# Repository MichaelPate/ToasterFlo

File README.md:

# ToasterFlo
 Control a toaster oven to make PCB assemblies

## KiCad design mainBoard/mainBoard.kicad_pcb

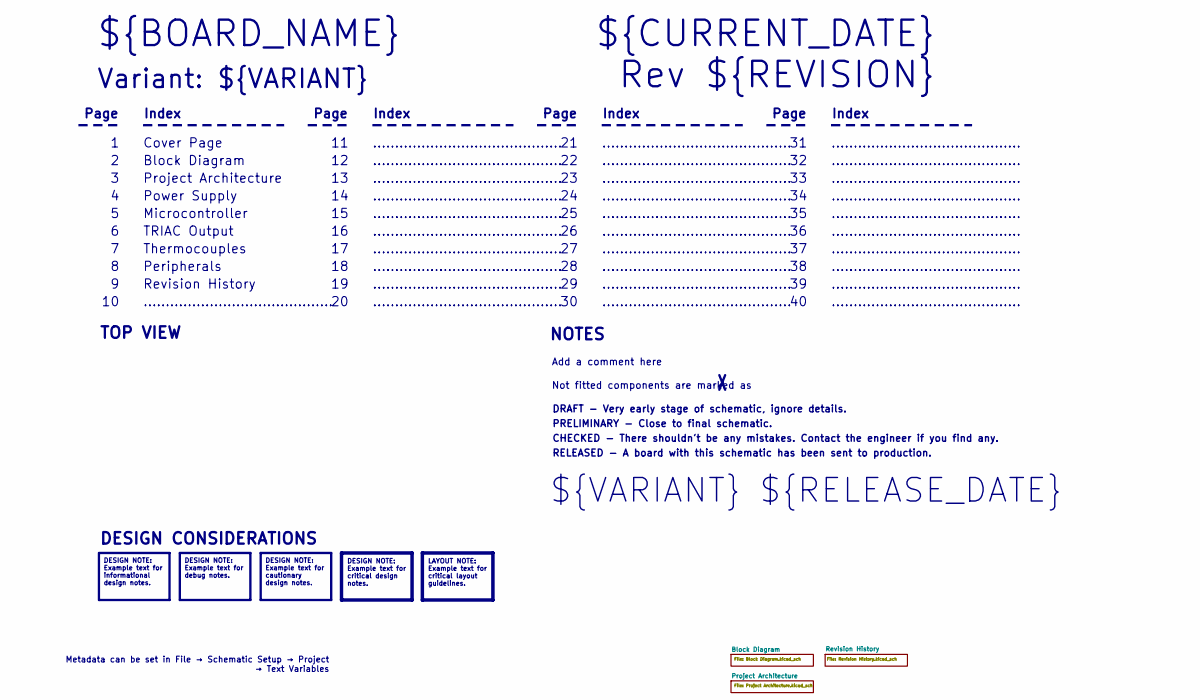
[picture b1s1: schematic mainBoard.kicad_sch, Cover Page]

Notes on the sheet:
...........................................
RELEASED - A board with this schematic has been sent to production.
Page
TOP VIEW
Revision History
Peripherals
Not fitted components are marked as
Index
PRELIMINARY - Close to final schematic.
${VARIANT} ${RELEASE_DATE}
Power Supply
${CURRENT_DATE}
Variant: ${VARIANT}
Rev ${REVISION}
Microcontroller
${BOARD_NAME}
DRAFT - Very early stage of schematic, ignore details.
TRIAC Output
Block Diagram
Add a comment here
Cover Page
NOTES
Project Architecture
CHECKED - There shouldn't be any mistakes. Contact the engineer if you find any.
DESIGN CONSIDERATIONS
Thermocouples
Metadata can be set in File → Schematic Setup → Project → Text Variables
DESIGN NOTE: Example text for informational design notes.
LAYOUT NOTE: Example text for critical layout guidelines.
DESIGN NOTE: Example text for cautionary design notes.
DESIGN NOTE: Example text for debug notes.
DESIGN NOTE: Example text for critical design notes.

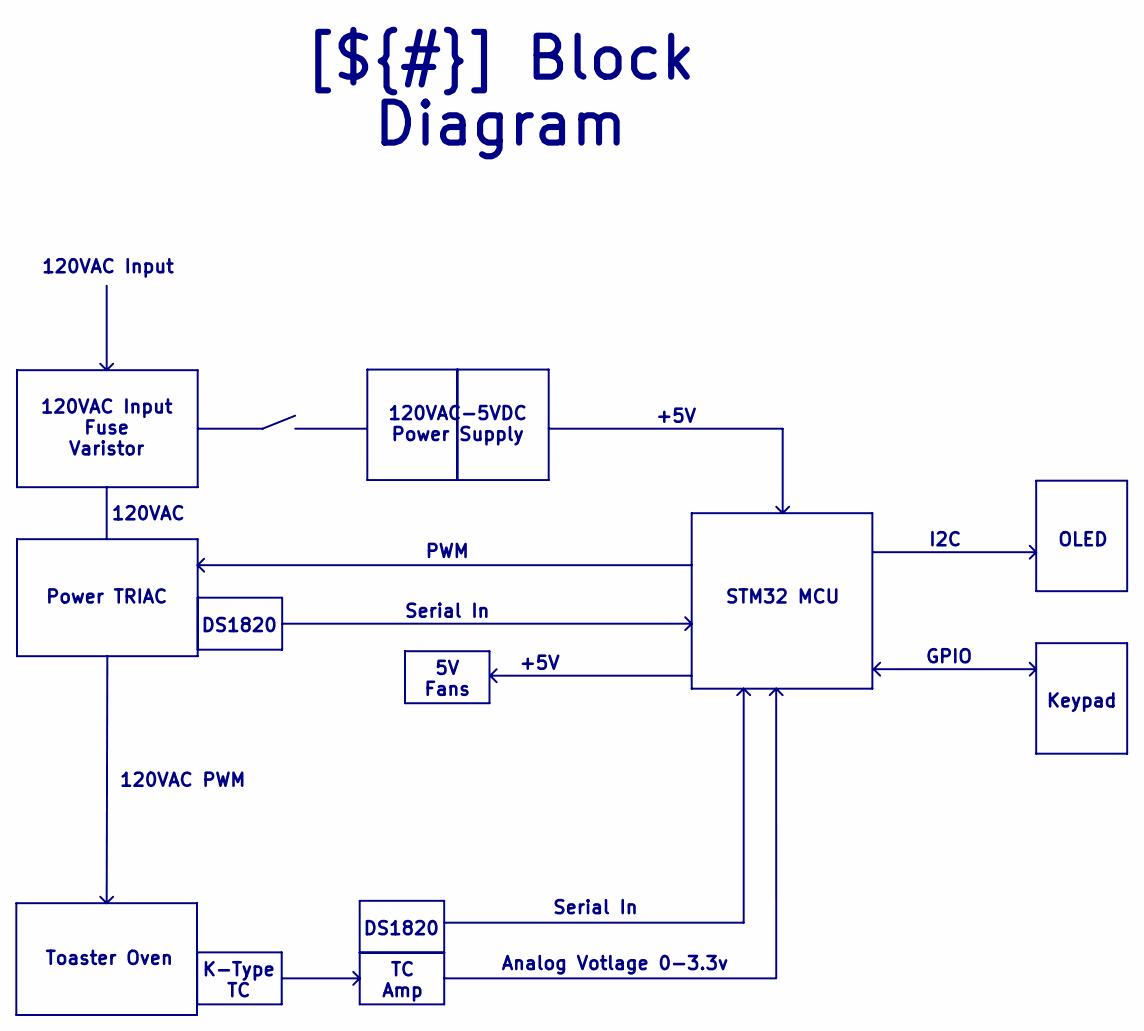
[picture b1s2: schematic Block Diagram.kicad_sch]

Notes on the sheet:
5V Fans
OLED
+5V
Serial In
GPIO
120VAC Input
TC Amp
K-Type TC
Toaster Oven
120VAC-5VDC Power Supply
120VAC Input Fuse Varistor
DS1820
Analog Votlage 0-3.3v
I2C
Power TRIAC
STM32 MCU
PWM
Keypad
120VAC PWM
120VAC
[${#}] ${TITLE}

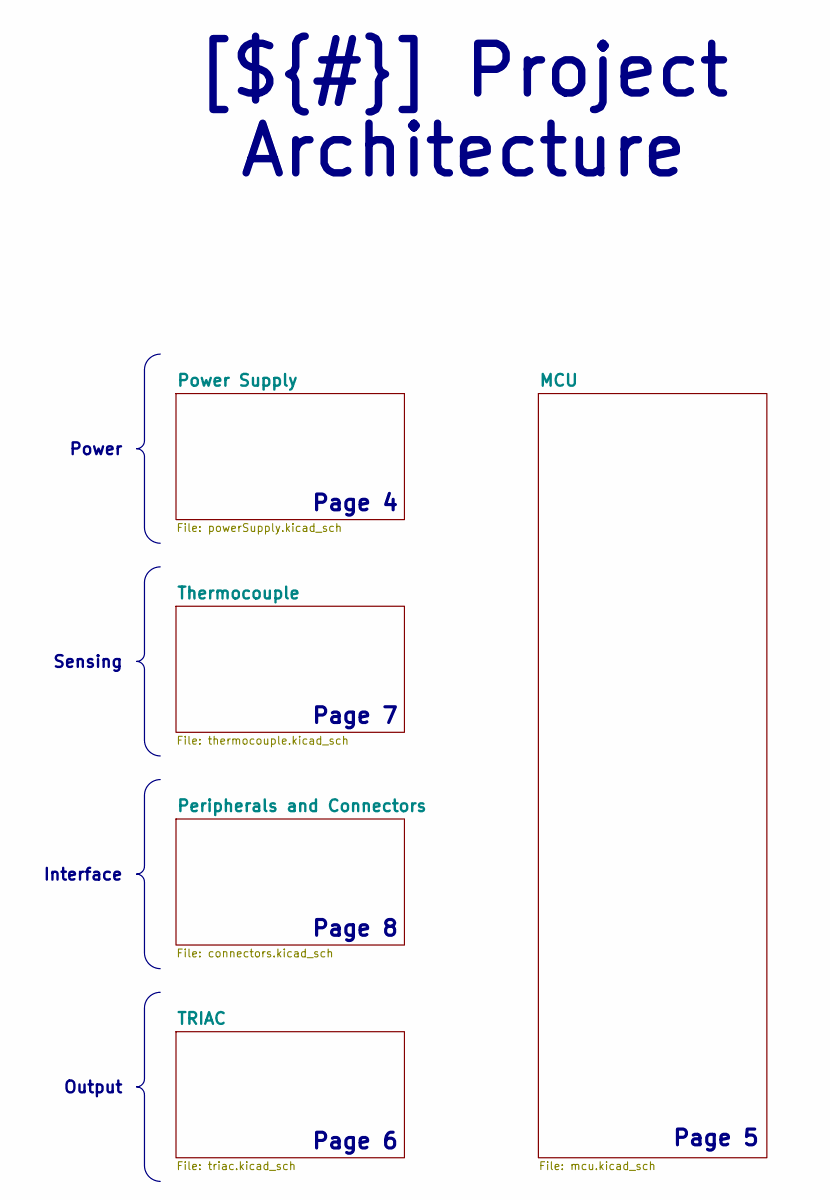
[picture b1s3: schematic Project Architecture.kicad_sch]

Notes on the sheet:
Page 7
Page 8
Page 6
Page 5
Page 4
Power
Sensing
[${#}] ${TITLE}
Interface
Output

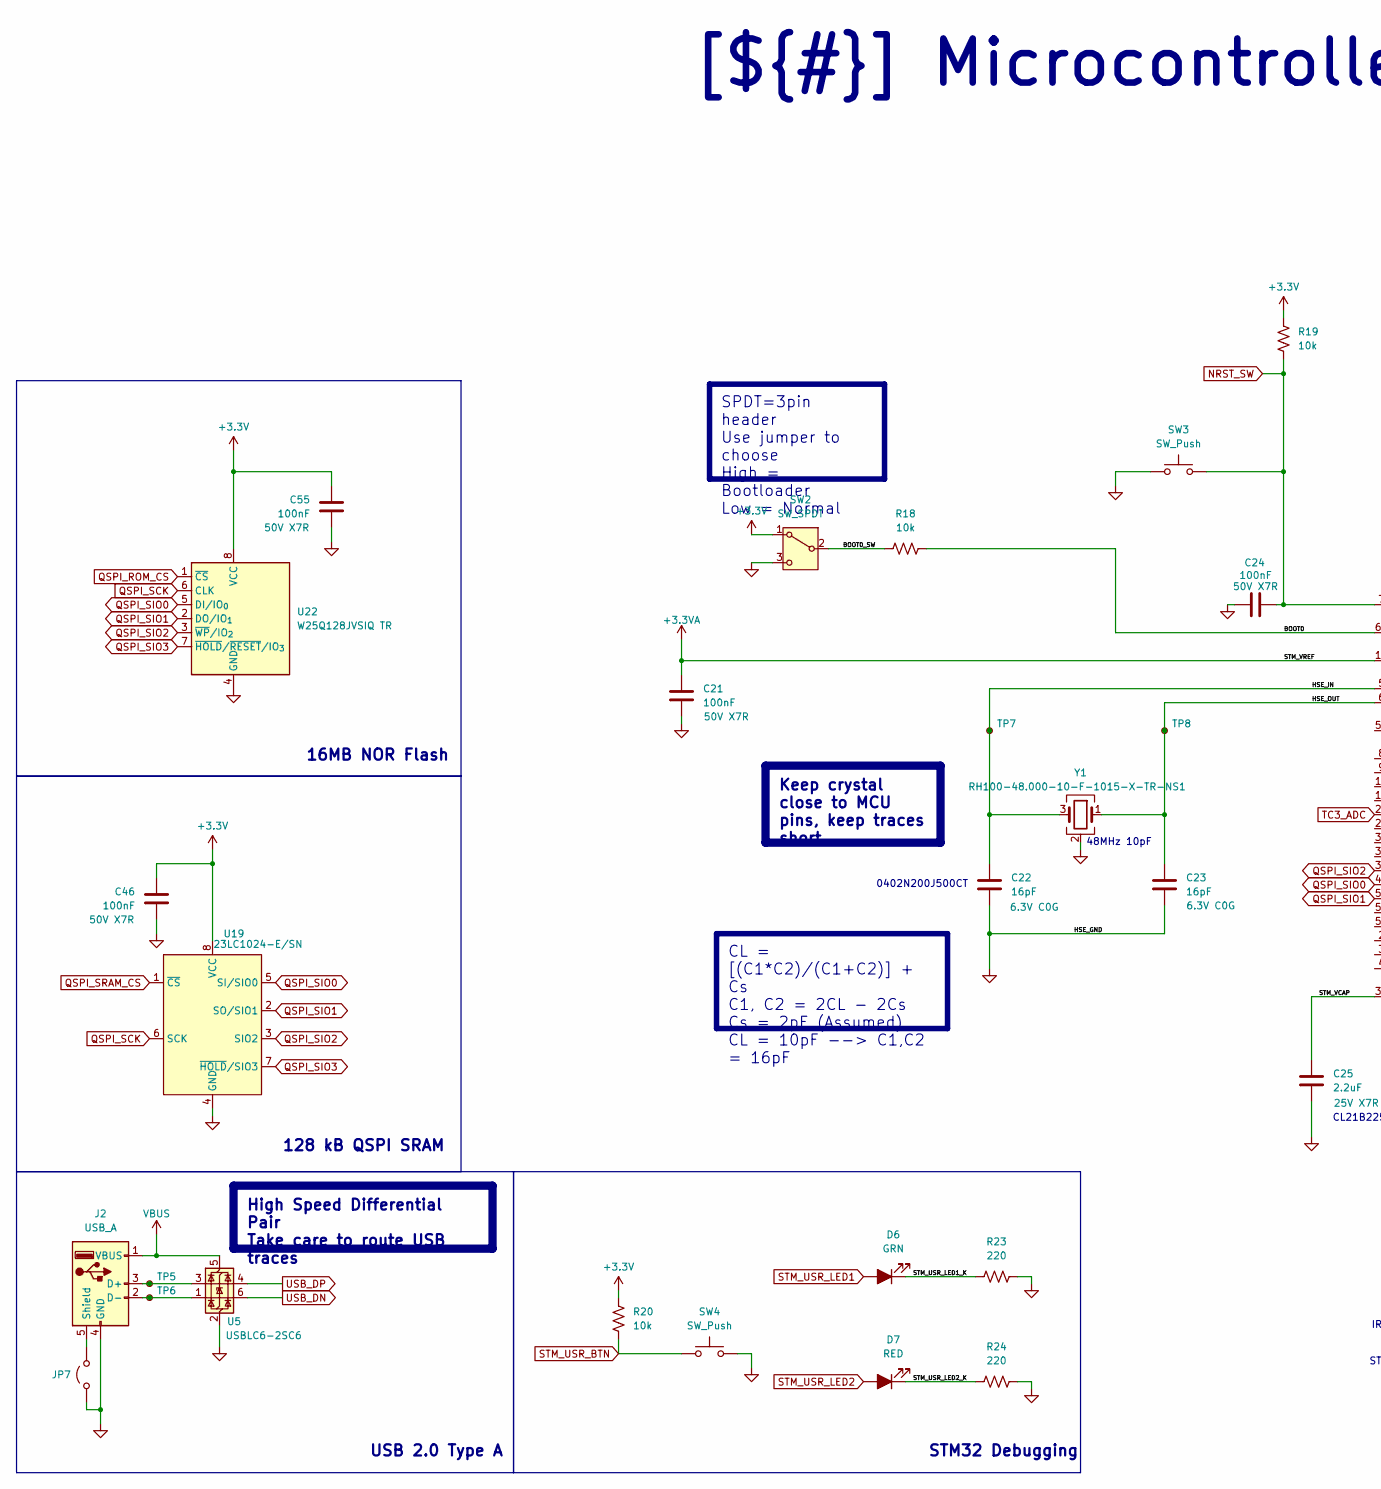
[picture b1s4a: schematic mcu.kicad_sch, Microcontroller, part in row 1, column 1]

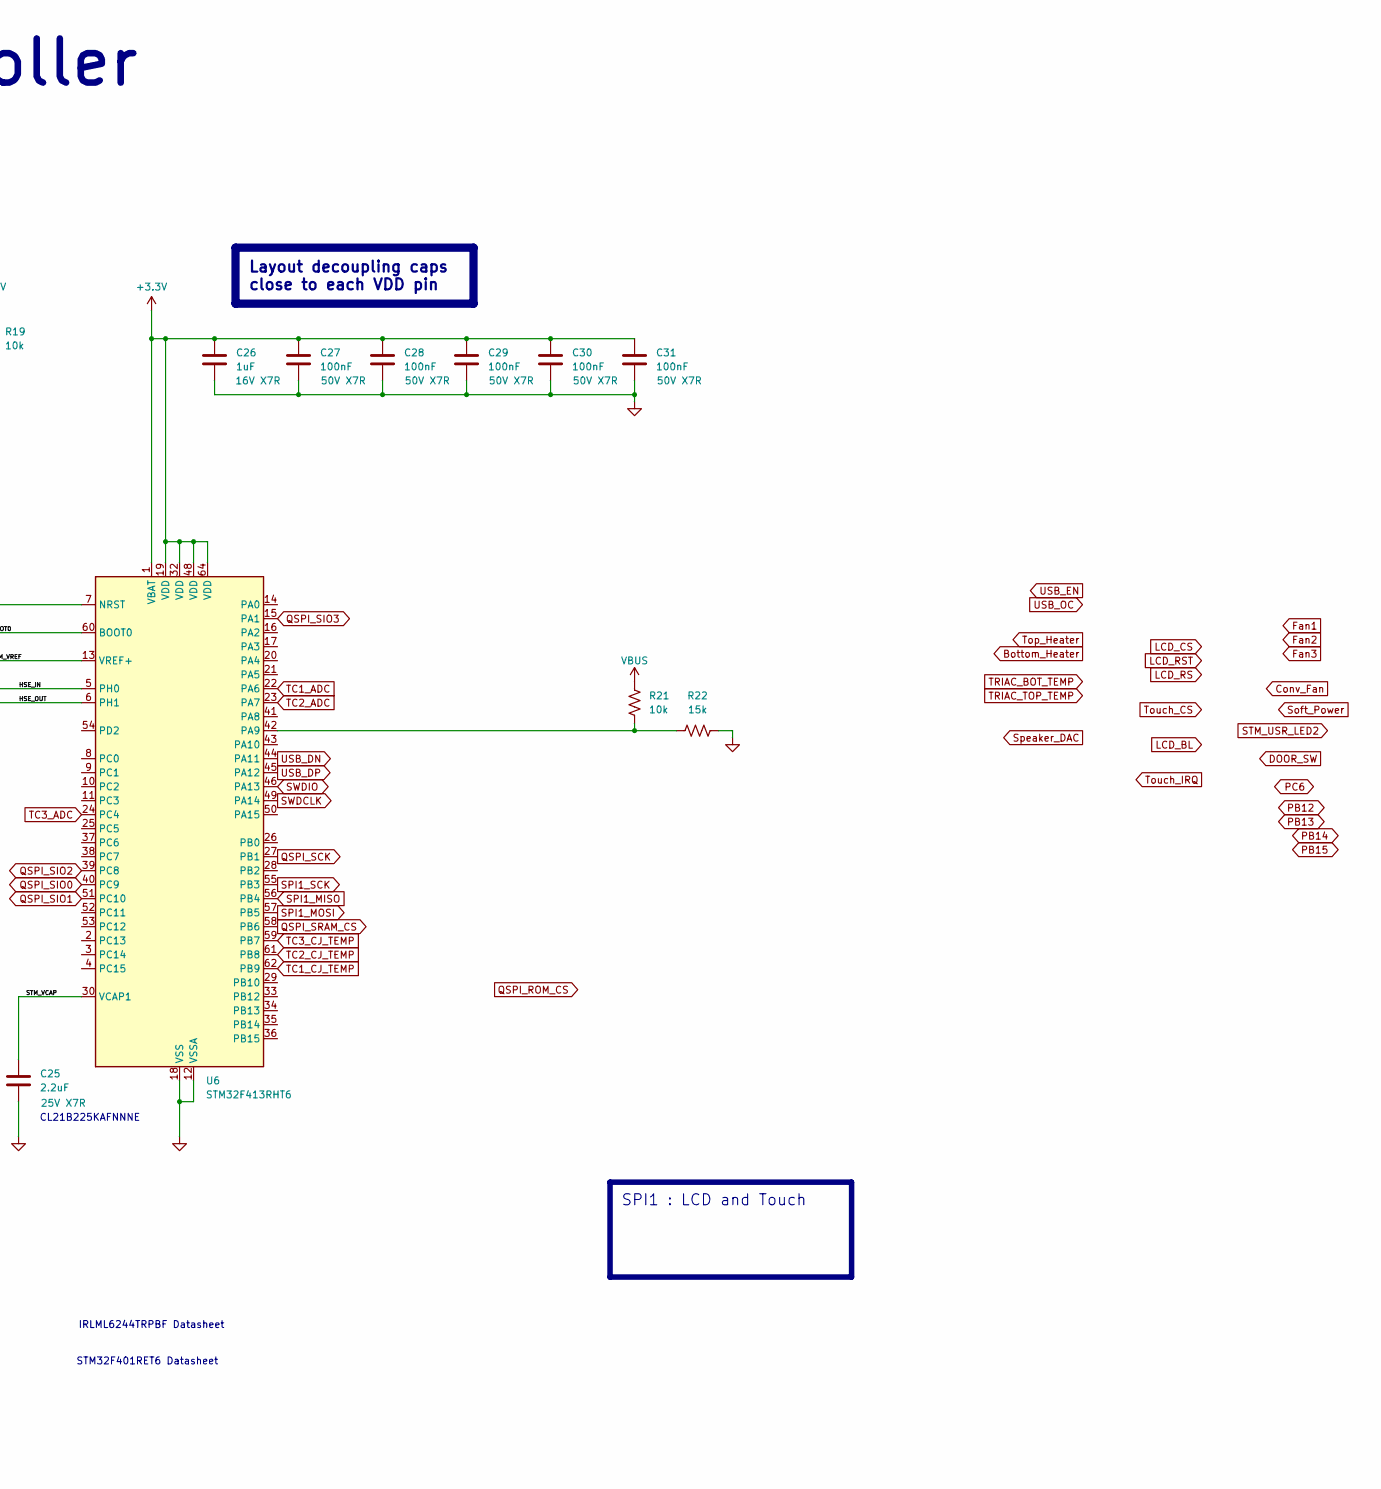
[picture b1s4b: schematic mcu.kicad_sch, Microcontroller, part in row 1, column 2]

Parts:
C21, C24, C27, C28, C29, C30, C31, C46, C55: 100nF; C_0603_1608Metric_Pad1.08x0.95mm_HandSolder
C22, C23: 16pF; C_0402_1005Metric_Pad0.74x0.62mm_HandSolder; part number 0402N200J500CT
C25: 2.2uF; C_0805_2012Metric_Pad1.18x1.45mm_HandSolder; part number CL21B225KAFNNNE
C26: 1uF; C_0805_2012Metric_Pad1.18x1.45mm_HandSolder
D6: GRN; LED_0603_1608Metric_Pad1.05x0.95mm_HandSolder
D7: RED; LED_0603_1608Metric_Pad1.05x0.95mm_HandSolder
J2: USB_A; USB_A_Connfly_DS1095
JP7: Jumper_2_Open; SolderJumper-2_P1.3mm_Open_TrianglePad1.0x1.5mm
R18, R19, R20, R21: 10k; R_0603_1608Metric_Pad0.98x0.95mm_HandSolder
R22: 15k; R_0603_1608Metric_Pad0.98x0.95mm_HandSolder
R23, R24: 220; R_0603_1608Metric_Pad0.98x0.95mm_HandSolder
SW2: SW_SPDT; PinHeader_1x03_P2.54mm_Vertical
SW3, SW4: SW_Push; SW_PUSH_6mm_H8.5mm
TP5, TP6, TP7, TP8: TestPoint_Small; TestPoint_Pad_D1.0mm
U5: USBLC6-2SC6; SOT-23-6
U6: STM32F413RHT6; LQFP-64_10x10mm_P0.5mm
U19: 23LC1024-E/SN; SOIC-8_5.3x5.3mm_P1.27mm
U22: W25Q128JVSIQ TR; SOIC-8_5.3x5.3mm_P1.27mm
Y1: RH100-48.000-10-F-1015-X-TR-NS1; Crystal_SMD_3225-4Pin_3.2x2.5mm

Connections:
+3.3V: C26.1, C27.1, C28.1, C29.1, C30.1, C31.1, C46.1, C55.1, R19.1, R20.1, SW2.1 (A), U6.1 (VBAT), U6.19 (VDD), U6.32 (VDD), U6.48 (VDD), U6.64 (VDD), U19.8 (VCC), U22.8 (VCC); also elsewhere on the board
+3.3VA: C21.1, U6.13 (VREF+); also elsewhere on the board
/Project Architecture/MCU/BOOT0: R18.2, U6.60 (BOOT0)
/Project Architecture/MCU/BOOT0_SW: R18.1, SW2.2 (B)
/Project Architecture/MCU/HSE_IN: C22.1, TP7.1 (1_1), U6.5 (PH0), Y1.3
/Project Architecture/MCU/HSE_OUT: C23.1, TP8.1 (1_1), U6.6 (PH1), Y1.1
/Project Architecture/MCU/STM_USR_LED1_K: D6.1 (K), R23.1
/Project Architecture/MCU/STM_USR_LED2_K: D7.1 (K), R24.1
/Project Architecture/MCU/STM_VCAP: C25.1, U6.30 (VCAP1)
GND: C21.2, C22.2, C23.2, C24.1, C25.2, C26.2, C27.2, C28.2, C29.2, C30.2, C31.2, C46.2, C55.2, J2.4 (GND), JP7.1 (A), R22.2, R23.2, R24.2, SW2.3 (C), SW3.1, SW4.2, U5.2 (GND), U6.12 (VSSA), U6.18 (VSS), U6.31 (VSS), U6.47 (VSS), U6.63 (VSS), U19.4 (GND), U22.4 (GND), Y1.2 (G), Y1.4 (G); also elsewhere on the board
NRST_SW: C24.2, R19.2, SW3.2, U6.7 (NRST); also elsewhere on the board
unnamed: J2.3 (D+), TP5.1 (1_1), U5.3 (I/O1)
unnamed: J2.2 (D-), TP6.1 (1_1), U5.1 (I/O2)
unnamed: J2.5 (Shield), JP7.2 (B)
unnamed: R21.1, R22.1, U6.42 (PA9)
QSPI_ROM_CS: U22.1 (~CS)
QSPI_SCK: U6.27 (PB1), U19.6 (SCK), U22.6 (CLK)
QSPI_SIO0: U6.40 (PC9), U19.5 (SI/SIO0), U22.5 (DI/IO_{0})
QSPI_SIO1: U6.51 (PC10), U19.2 (SO/SIO1), U22.2 (DO/IO_{1})
QSPI_SIO2: U6.39 (PC8), U19.3 (SIO2), U22.3 (~WP/IO_{2})
QSPI_SIO3: U6.15 (PA1), U19.7 (~HOLD/SIO3), U22.7 (~HOLD/~RESET/IO_{3})
QSPI_SRAM_CS: U6.58 (PB6), U19.1 (~CS)
SPI1_MISO: U6.56 (PB4); also elsewhere on the board
SPI1_MOSI: U6.57 (PB5); also elsewhere on the board
SPI1_SCK: U6.55 (PB3); also elsewhere on the board
STM_USR_BTN: R20.2, SW4.1
STM_USR_LED1: D6.2 (A)
STM_USR_LED2: D7.2 (A)
SWDCLK: U6.49 (PA14); also elsewhere on the board
SWDIO: U6.46 (PA13); also elsewhere on the board
TC1_ADC: U6.22 (PA6); also elsewhere on the board
TC1_CJ_TEMP: U6.62 (PB9); also elsewhere on the board
TC2_ADC: U6.23 (PA7); also elsewhere on the board
TC2_CJ_TEMP: U6.61 (PB8); also elsewhere on the board
TC3_ADC: U6.24 (PC4); also elsewhere on the board
TC3_CJ_TEMP: U6.59 (PB7); also elsewhere on the board
USB_DN: U5.6 (I/O2), U6.44 (PA11)
USB_DP: U5.4 (I/O1), U6.45 (PA12)
VBUS: J2.1 (VBUS), R21.2, U5.5 (VBUS); also elsewhere on the board

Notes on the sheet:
STM32 Debugging
CL21B225KAFNNNE
USB 2.0 Type A
STM32F401RET6 Datasheet
0402N200J500CT
16MB NOR Flash
128 kB QSPI SRAM
48MHz 10pF
IRLML6244TRPBF Datasheet
High Speed Differential Pair Take care to route USB traces
Layout decoupling caps close to each VDD pin
Keep crystal close to MCU pins, keep traces short
SPI1 : LCD and Touch
CL = [(C1*C2)/(C1+C2)] + Cs C1, C2 = 2CL - 2Cs Cs = 2pF (Assumed) CL = 10pF --> C1,C2 = 16pF
[${#}] ${TITLE}
SPDT=3pin header Use jumper to choose High = Bootloader Low = Normal

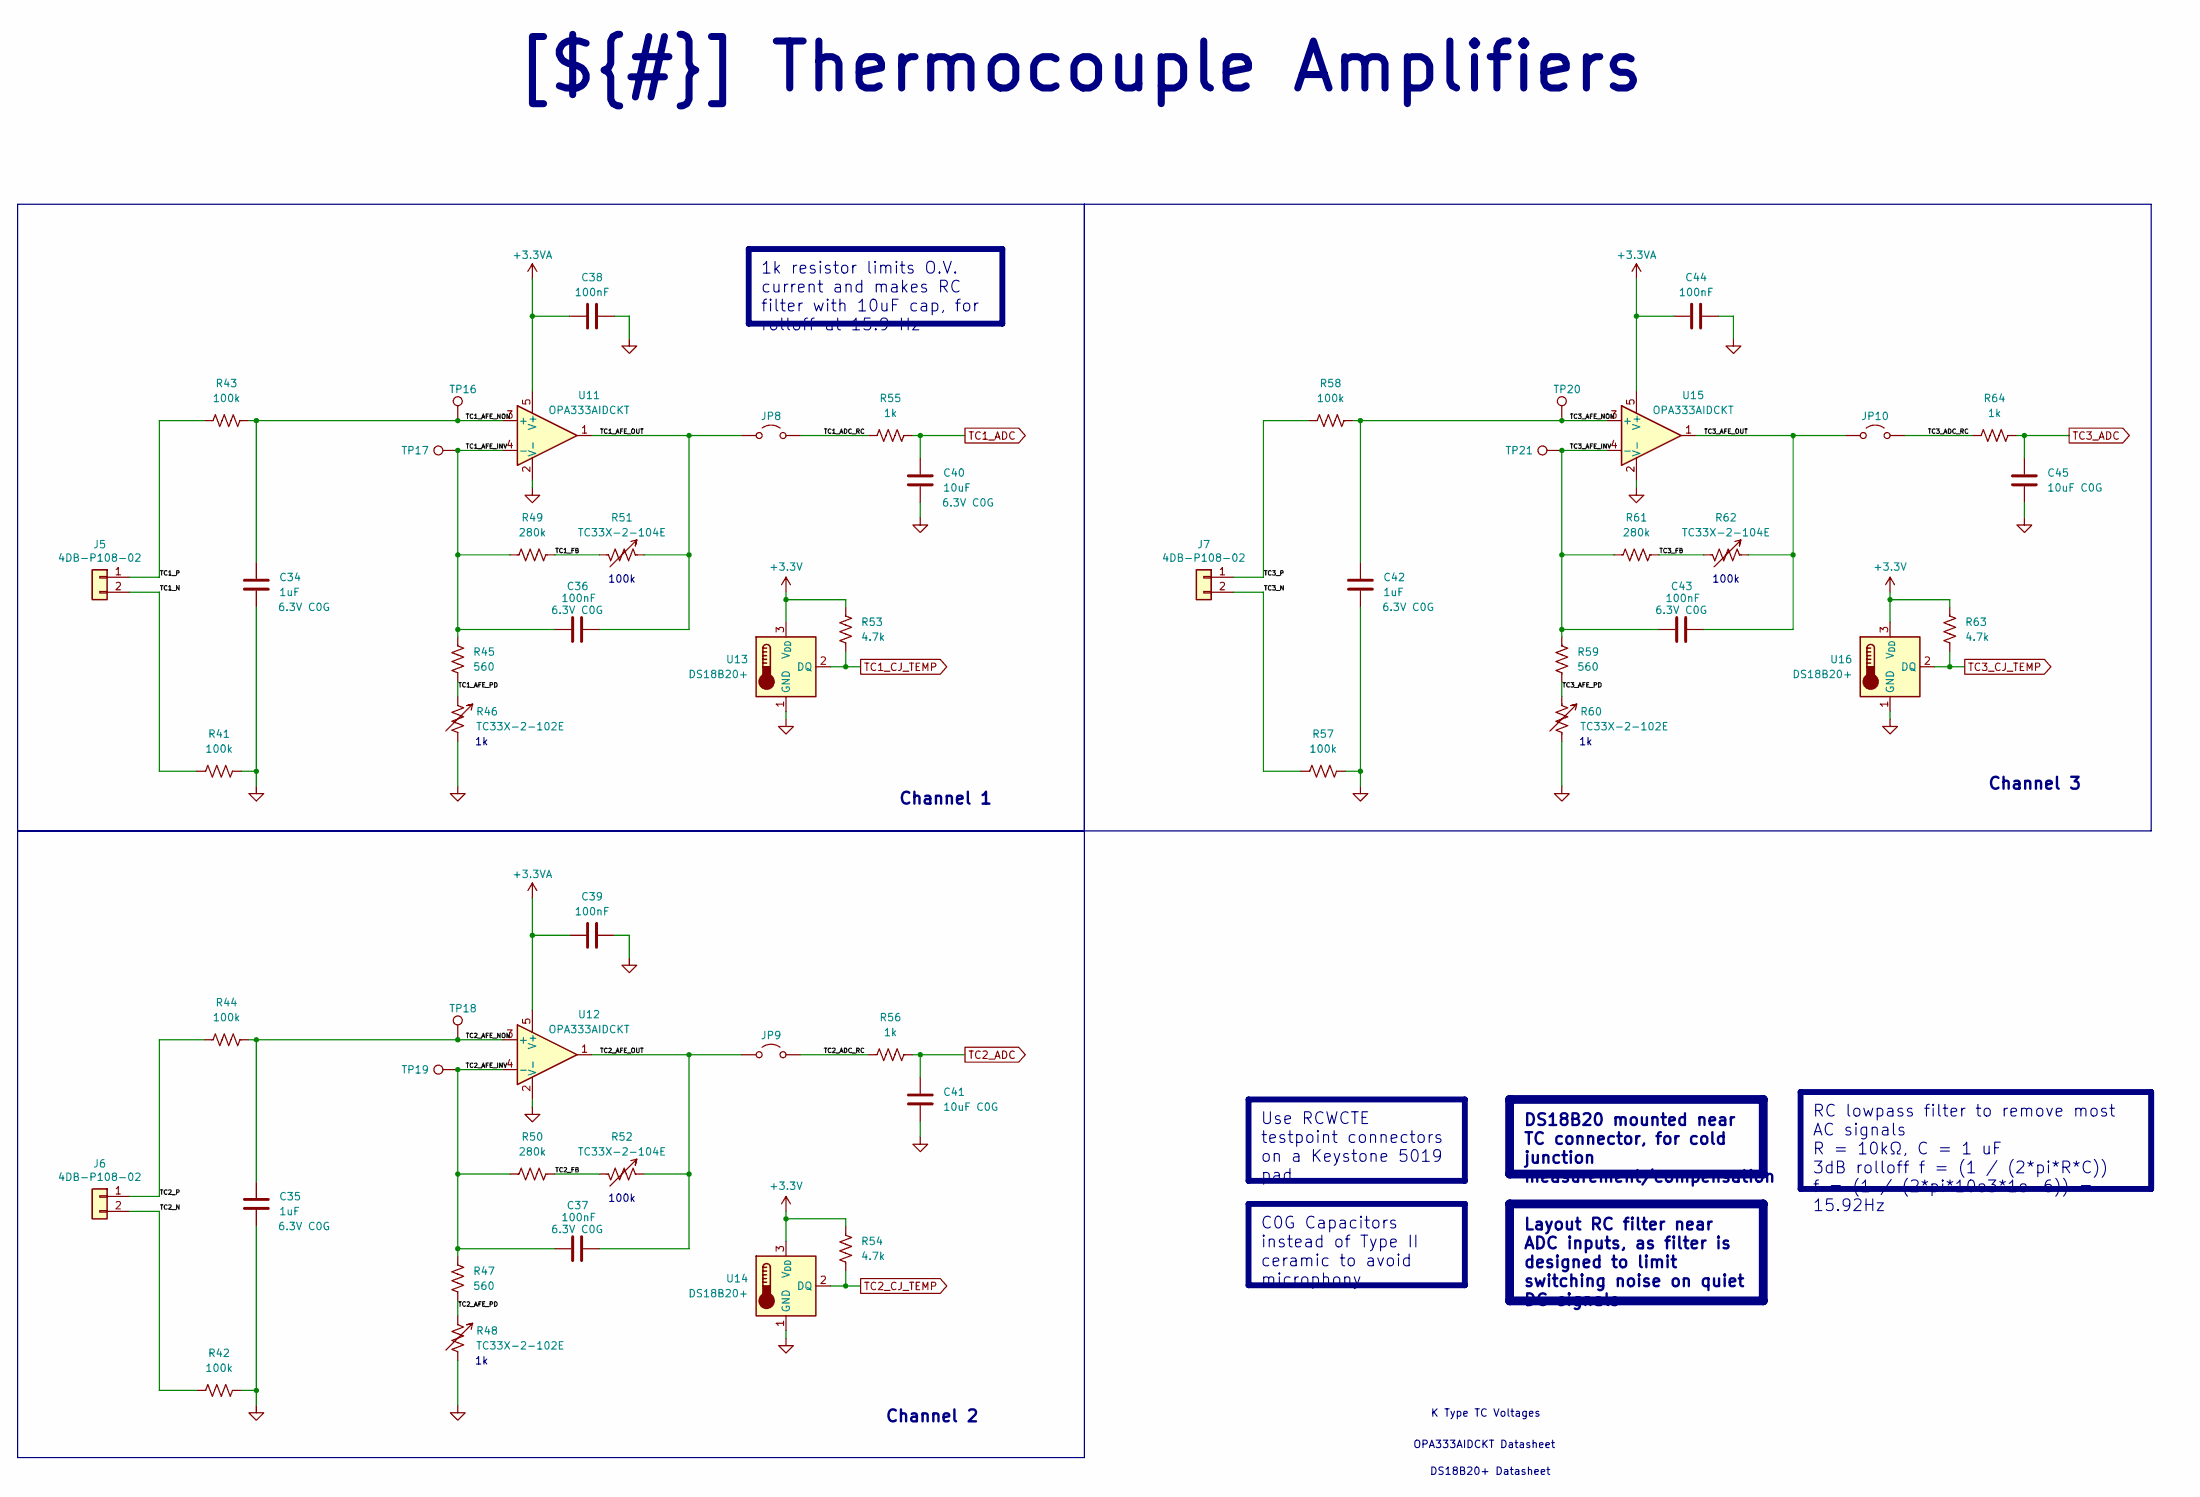
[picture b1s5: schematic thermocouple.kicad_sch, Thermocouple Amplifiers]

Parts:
C34, C35, C42: 1uF; C_0603_1608Metric_Pad1.08x0.95mm_HandSolder
C36, C37, C43: 100nF; C_0603_1608Metric_Pad1.08x0.95mm_HandSolder
C38, C39, C44: 100nF; C_0805_2012Metric_Pad1.18x1.45mm_HandSolder
C40: 10uF; C_0603_1608Metric_Pad1.08x0.95mm_HandSolder
C41, C45: 10uF C0G; C_0603_1608Metric_Pad1.08x0.95mm_HandSolder
J5, J6, J7: 4DB-P108-02; CONN_4DB-P108-02_TEC
JP8, JP9, JP10: Jumper_2_Open; SolderJumper-2_P1.3mm_Open_TrianglePad1.0x1.5mm
R41, R42, R43, R44, R57, R58: 100k; R_0603_1608Metric_Pad0.98x0.95mm_HandSolder
R45, R47, R59: 560; R_0603_1608Metric_Pad0.98x0.95mm_HandSolder
R46, R48, R60: TC33X-2-102E; Potentiometer_Bourns_TC33X_Vertical
R49, R50, R61: 280k; R_0603_1608Metric_Pad0.98x0.95mm_HandSolder
R51, R52, R62: TC33X-2-104E; Potentiometer_Bourns_TC33X_Vertical
R53, R54, R63: 4.7k; R_0603_1608Metric_Pad0.98x0.95mm_HandSolder
R55, R56, R64: 1k; R_0603_1608Metric_Pad0.98x0.95mm_HandSolder
TP16, TP17, TP18, TP19, TP20, TP21: TestPoint; TestPoint_Pad_D1.5mm
U11, U12, U15: OPA333AIDCKT; SOIC-8_3.9x4.9mm_P1.27mm
U13, U14, U16: DS18B20+; TO-92_Inline

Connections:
+3.3V: R53.1, R54.1, R63.1, U13.3 (V_{DD}), U14.3 (V_{DD}), U16.3 (V_{DD}); also elsewhere on the board
+3.3VA: C38.1, C39.1, C44.1, U11.5 (V+), U12.5 (V+), U15.5 (V+); also elsewhere on the board
/Project Architecture/Thermocouple/TC1_ADC_RC: JP8.2 (B), R55.1
/Project Architecture/Thermocouple/TC1_AFE_INV: C36.1, R45.1, R49.1, TP17.1 (1_1), U11.4 (-)
/Project Architecture/Thermocouple/TC1_AFE_NON: C34.1, R43.2, TP16.1 (1_1), U11.3 (+)
/Project Architecture/Thermocouple/TC1_AFE_OUT: C36.2, JP8.1 (A), R51.1, U11.1
/Project Architecture/Thermocouple/TC1_AFE_PD: R45.2, R46.1
/Project Architecture/Thermocouple/TC1_FB: R49.2, R51.2
/Project Architecture/Thermocouple/TC1_N: J5.2, R41.1
/Project Architecture/Thermocouple/TC1_P: J5.1, R43.1
/Project Architecture/Thermocouple/TC2_ADC_RC: JP9.2 (B), R56.1
/Project Architecture/Thermocouple/TC2_AFE_INV: C37.1, R47.1, R50.1, TP19.1 (1_1), U12.4 (-)
/Project Architecture/Thermocouple/TC2_AFE_NON: C35.1, R44.2, TP18.1 (1_1), U12.3 (+)
/Project Architecture/Thermocouple/TC2_AFE_OUT: C37.2, JP9.1 (A), R52.1, U12.1
/Project Architecture/Thermocouple/TC2_AFE_PD: R47.2, R48.1
/Project Architecture/Thermocouple/TC2_FB: R50.2, R52.2
/Project Architecture/Thermocouple/TC2_N: J6.2, R42.1
/Project Architecture/Thermocouple/TC2_P: J6.1, R44.1
/Project Architecture/Thermocouple/TC3_ADC_RC: JP10.2 (B), R64.1
/Project Architecture/Thermocouple/TC3_AFE_INV: C43.1, R59.1, R61.1, TP21.1 (1_1), U15.4 (-)
/Project Architecture/Thermocouple/TC3_AFE_NON: C42.1, R58.2, TP20.1 (1_1), U15.3 (+)
/Project Architecture/Thermocouple/TC3_AFE_OUT: C43.2, JP10.1 (A), R62.1, U15.1
/Project Architecture/Thermocouple/TC3_AFE_PD: R59.2, R60.1
/Project Architecture/Thermocouple/TC3_FB: R61.2, R62.2
/Project Architecture/Thermocouple/TC3_N: J7.2, R57.1
/Project Architecture/Thermocouple/TC3_P: J7.1, R58.1
GND: C34.2, C35.2, C38.2, C39.2, C40.2, C41.2, C42.2, C44.2, C45.2, R41.2, R42.2, R46.2, R48.2, R57.2, R60.2, U11.2 (V-), U12.2 (V-), U13.1 (GND), U14.1 (GND), U15.2 (V-), U16.1 (GND); also elsewhere on the board
TC1_ADC: C40.1, R55.2; also elsewhere on the board
TC1_CJ_TEMP: R53.2, U13.2 (DQ); also elsewhere on the board
TC2_ADC: C41.1, R56.2; also elsewhere on the board
TC2_CJ_TEMP: R54.2, U14.2 (DQ); also elsewhere on the board
TC3_ADC: C45.1, R64.2; also elsewhere on the board
TC3_CJ_TEMP: R63.2, U16.2 (DQ); also elsewhere on the board

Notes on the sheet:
DS18B20+ Datasheet
Channel 1
100k
Channel 3
Channel 2
K Type TC Voltages
OPA333AIDCKT Datasheet
Layout RC filter near ADC inputs, as filter is designed to limit switching noise on quiet DC signals
1k resistor limits O.V. current and makes RC filter with 10uF cap, for rolloff at 15.9 Hz
DS18B20 mounted near TC connector, for cold junction measurement/compensation
RC lowpass filter to remove most AC signals R = 10kΩ, C = 1 uF 3dB rolloff f = (1 / (2*pi*R*C)) f = (1 / (2*pi*10e3*1e-6)) = 15.92Hz
Use RCWCTE testpoint connectors on a Keystone 5019 pad
[${#}] ${TITLE}
C0G Capacitors instead of Type II ceramic to avoid microphony

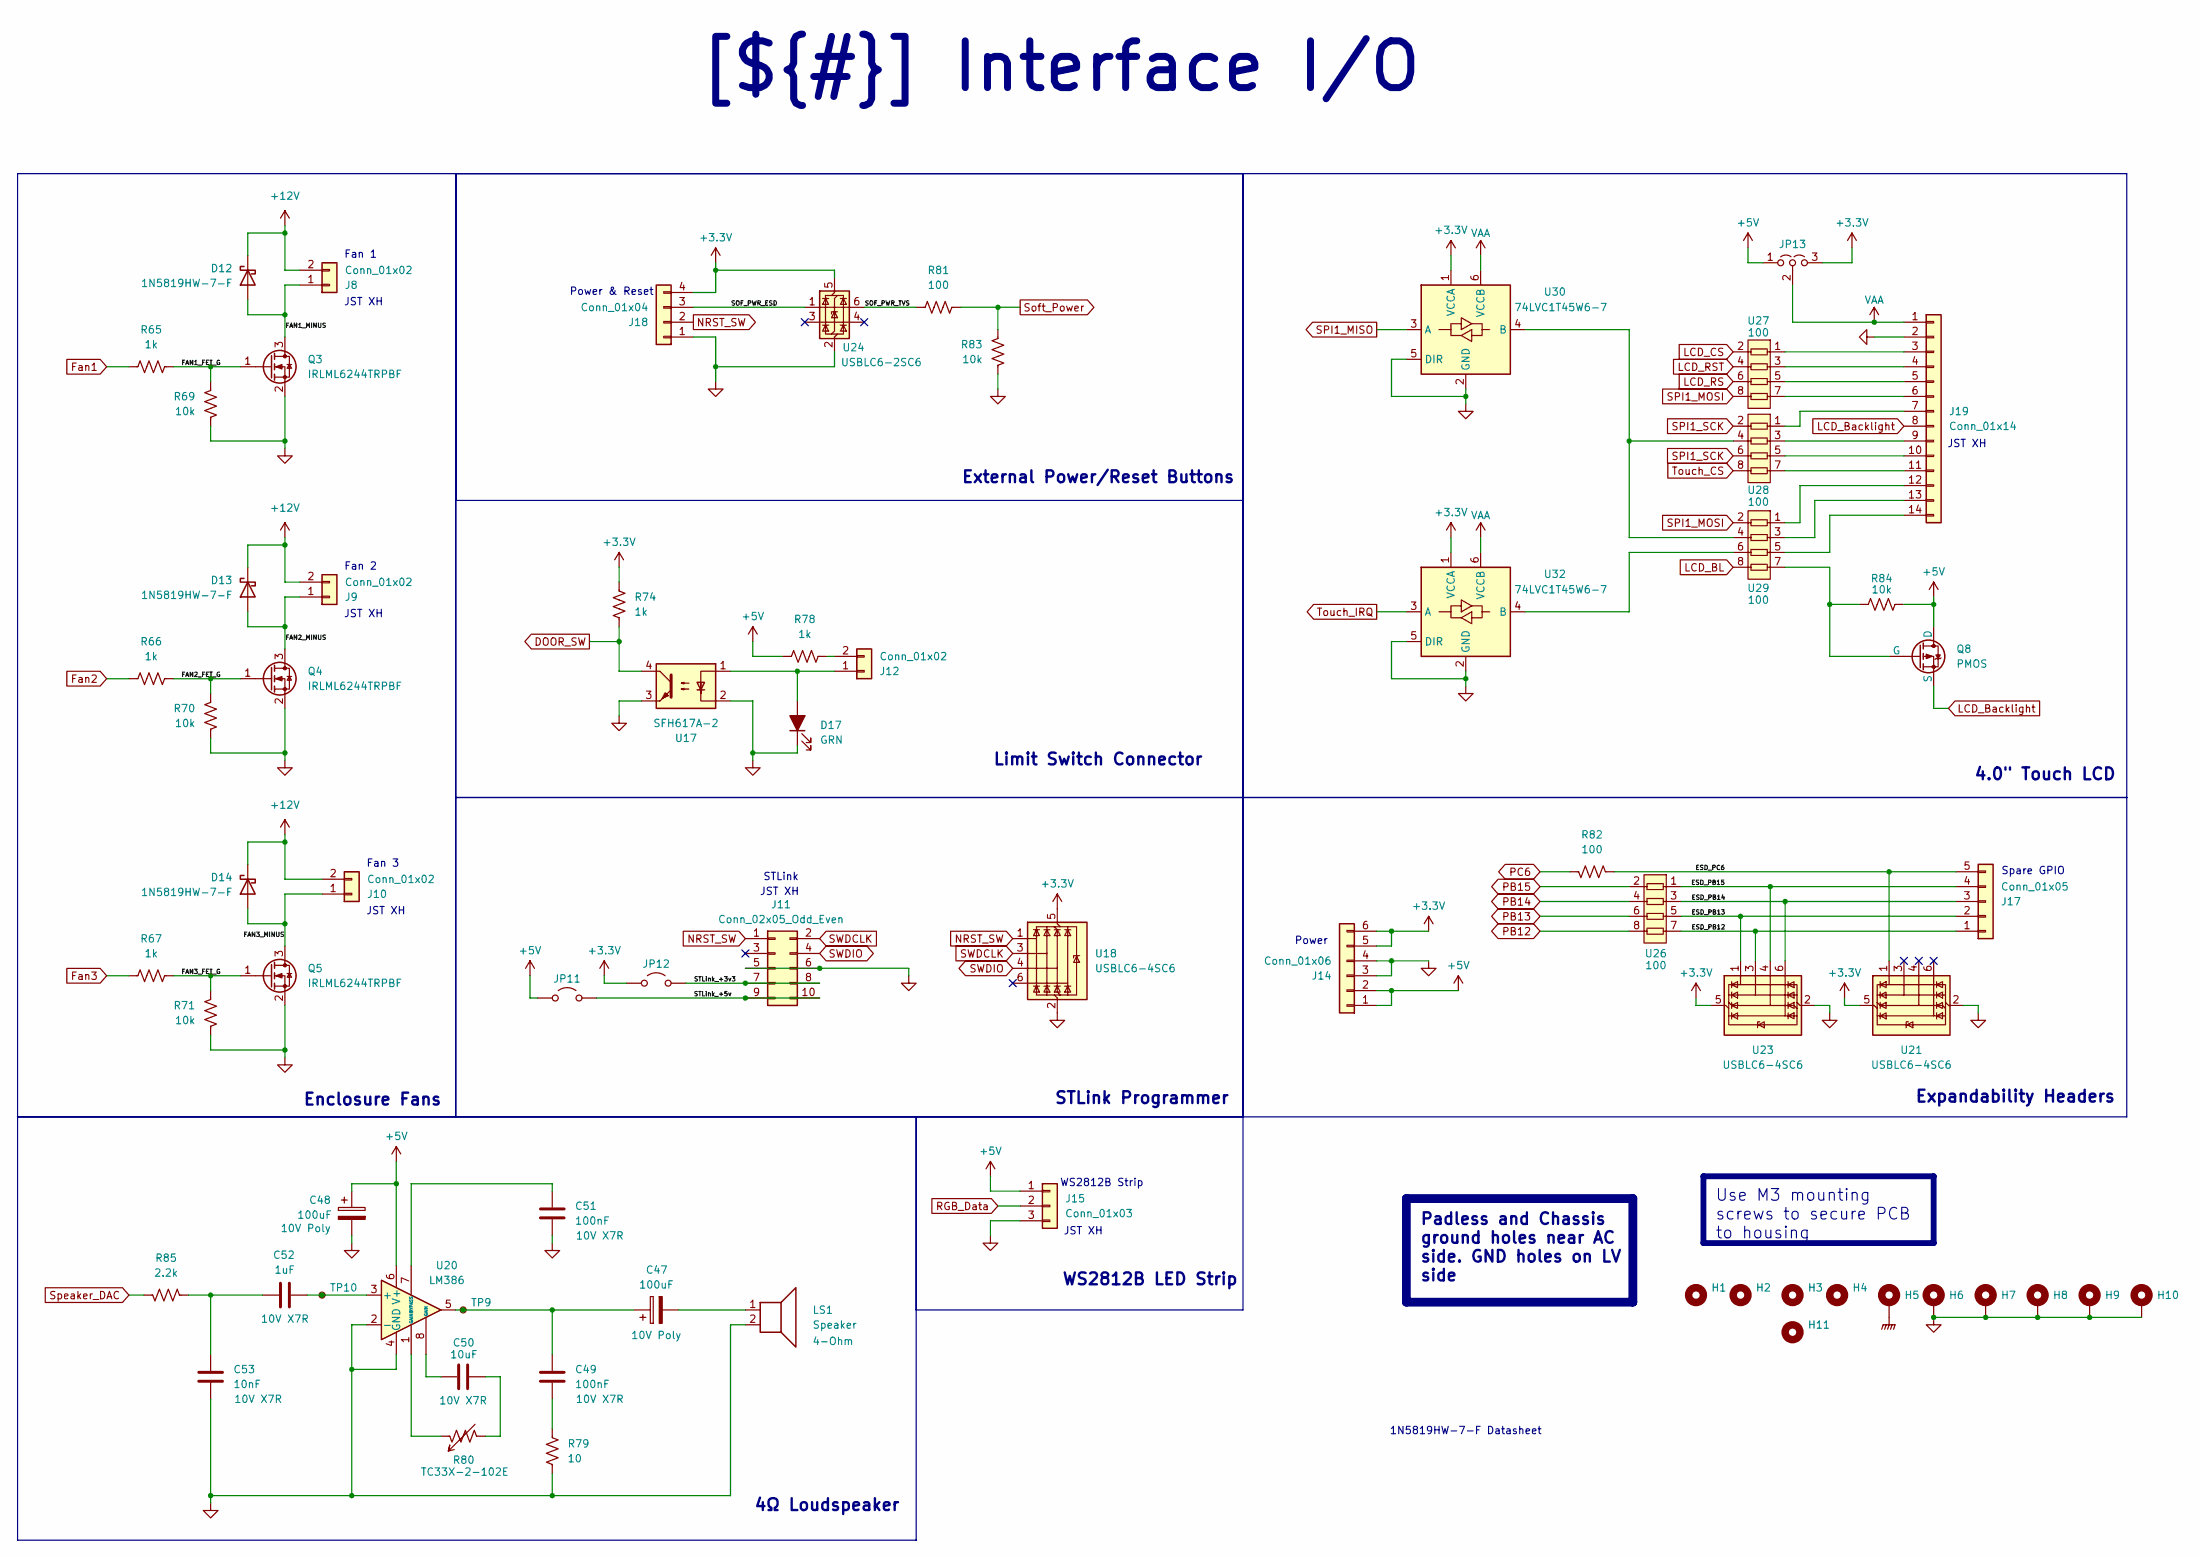
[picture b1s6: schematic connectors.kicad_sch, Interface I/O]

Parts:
C47, C48: 100uF; C_Elec_6.3x5.8; part number A768EB476M1VLAE042
C49, C51: 100nF; C_0805_2012Metric_Pad1.18x1.45mm_HandSolder; part number CL31A226MOCLNNC
C50: 10uF; C_0805_2012Metric_Pad1.18x1.45mm_HandSolder; part number CL31A226MOCLNNC
C52: 1uF; C_0805_2012Metric_Pad1.18x1.45mm_HandSolder; part number CL31A226MOCLNNC
C53: 10nF; C_0603_1608Metric_Pad1.08x0.95mm_HandSolder; part number CL31A226MOCLNNC
D12, D13, D14: 1N5819HW-7-F; D_SOD-123
D17: GRN; LED_0603_1608Metric_Pad1.05x0.95mm_HandSolder
H1, H2, H3, H4, H11: MountingHole; MountingHole_3.2mm_M3
H5, H6, H7, H8, H9, H10: MountingHole_Pad; MountingHole_3.2mm_M3_Pad_Via
J8, J9, J10: Conn_01x02; JST_XH_B2B-XH-A_1x02_P2.50mm_Vertical
J11: Conn_02x05_Odd_Even; IDC-Header_2x05_P2.54mm_Vertical
J12: Conn_01x02; TerminalBlock_Phoenix_MKDS-1,5-2-5.08_1x02_P5.08mm_Horizont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
J14: Conn_01x06; PinHeader_1x06_P2.54mm_Vertical
J15: Conn_01x03; JST_XH_B3B-XH-A_1x03_P2.50mm_Vertical
J17: Conn_01x05; PinHeader_1x05_P2.54mm_Vertical
J18: Conn_01x04; JST_XH_B4B-XH-A_1x04_P2.50mm_Vertical
J19: Conn_01x14; JST_XH_B14B-XH-A_1x14_P2.50mm_Vertical
JP11, JP12: Jumper_2_Open; SolderJumper-2_P1.3mm_Open_TrianglePad1.0x1.5mm
JP13: Jumper_3_Open; SolderJumper-3_P1.3mm_Open_RoundedPad1.0x1.5mm
LS1: Speaker; JST_PH_B2B-PH-K_1x02_P2.00mm_Vertical
Q3, Q4, Q5: IRLML6244TRPBF; SOT-23
Q8: PMOS; SOT-23
R65, R66, R67, R74, R78: 1k; R_0603_1608Metric_Pad0.98x0.95mm_HandSolder
R69, R70, R71, R83, R84: 10k; R_0603_1608Metric_Pad0.98x0.95mm_HandSolder
R79: 10; R_0603_1608Metric_Pad0.98x0.95mm_HandSolder
R80: TC33X-2-102E; Potentiometer_Bourns_TC33X_Vertical
R81, R82: 100; R_0603_1608Metric_Pad0.98x0.95mm_HandSolder
R85: 2.2k; R_0603_1608Metric_Pad0.98x0.95mm_HandSolder
TP9, TP10: TestPoint_Small; TestPoint_Pad_D1.0mm
U17: SFH617A-2; DIP-4_W7.62mm
U18, U21, U23: USBLC6-4SC6; SOT-23-6
U20: LM386; SOIC-8_3.9x4.9mm_P1.27mm
U24: USBLC6-2SC6; SOT-23-6
U26, U27, U28, U29: 100; R_Array_Convex_4x1206; part number RAVF164DJT100R
U30, U32: 74LVC1T45W6-7; SOT-23-6

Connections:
+3.3V: J14.5, J14.6, J18.4, JP12.1 (A), JP13.3 (B), R74.1, U18.5 (VBUS), U21.5 (VBUS), U23.5 (VBUS), U24.5 (VBUS), U30.1 (VCCA), U32.1 (VCCA); also elsewhere on the board
+5V: C48.1, J14.1, J14.2, J15.1, JP11.1 (A), JP13.1 (A), Q8.1 (D), R78.2, R84.2, U20.6 (V+); also elsewhere on the board
+12V: D12.1 (K), D13.1 (K), D14.1 (K), J8.2, J9.2, J10.2; also elsewhere on the board
/Project Architecture/Peripherals and Connectors/ESD_PB12: J17.1, U23.3 (I/O2), U26.7
/Project Architecture/Peripherals and Connectors/ESD_PB13: J17.2, U23.1 (I/O1), U26.5
/Project Architecture/Peripherals and Connectors/ESD_PB14: J17.3, U23.6 (I/O4), U26.3
/Project Architecture/Peripherals and Connectors/ESD_PB15: J17.4, U23.4 (I/O3), U26.1
/Project Architecture/Peripherals and Connectors/ESD_PC6: J17.5, R82.1, U21.1 (I/O1)
/Project Architecture/Peripherals and Connectors/FAN1_FET_G: Q3.1 (G), R65.2, R69.1
/Project Architecture/Peripherals and Connectors/FAN1_MINUS: D12.2 (A), J8.1, Q3.3 (D)
/Project Architecture/Peripherals and Connectors/FAN2_FET_G: Q4.1 (G), R66.2, R70.1
/Project Architecture/Peripherals and Connectors/FAN2_MINUS: D13.2 (A), J9.1, Q4.3 (D)
/Project Architecture/Peripherals and Connectors/FAN3_FET_G: Q5.1 (G), R67.2, R71.1
/Project Architecture/Peripherals and Connectors/FAN3_MINUS: D14.2 (A), J10.1, Q5.3 (D)
/Project Architecture/Peripherals and Connectors/SOF_PWR_ESD: J18.3, U24.1 (I/O1)
/Project Architecture/Peripherals and Connectors/SOF_PWR_TVS: R81.1, U24.6 (I/O1)
/Project Architecture/Peripherals and Connectors/STLink_+3v3: J11.7, J11.8, JP12.2 (B)
/Project Architecture/Peripherals and Connectors/STLink_+5v: J11.9, J11.10, JP11.2 (B)
DOOR_SW: R74.2, U17.4
Fan1: R65.1
Fan2: R66.1
Fan3: R67.1
GND: C48.2, C51.2, C53.2, D17.1 (K), H6.1 (1_1), H7.1 (1_1), H8.1 (1_1), H9.1 (1_1), H10.1 (1_1), J11.5, J11.6, J14.3, J14.4, J15.3, J18.1, J19.2, LS1.2, Q3.2 (S), Q4.2 (S), Q5.2 (S), R69.2, R70.2, R71.2, R79.2, R83.2, U17.2, U17.3, U18.2 (GND), U20.2 (-), U20.4 (GND), U21.2 (GND), U23.2 (GND), U24.2 (GND), U30.2 (GND), U30.5 (DIR), U32.2 (GND), U32.5 (DIR); also elsewhere on the board
GNDPWR: H5.1 (1_1); also elsewhere on the board
LCD_BL: U29.8
LCD_Backlight: J19.8, Q8.3 (S)
LCD_CS: U27.2
LCD_RS: U27.6
LCD_RST: U27.4
NRST_SW: J11.1, J18.2, U18.1 (I/O1); also elsewhere on the board
unnamed: C47.1, C49.1, TP9.1 (1_1), U20.5
unnamed: C47.2, LS1.1
unnamed: C49.2, R79.1
unnamed: C50.1, U20.8 (GAIN)
unnamed: C50.2, R80.2
unnamed: C52.1, C53.1, R85.1
unnamed: D17.2 (A), J12.1, U17.1
unnamed: J12.2, R78.1
unnamed: J19.3, U27.1
unnamed: J19.4, U27.3
unnamed: J19.5, U27.5
unnamed: J19.6, U27.7
unnamed: J19.7, U28.1
unnamed: J19.9, U28.3
unnamed: J19.10, U28.5
unnamed: J19.11, U28.7
unnamed: J19.12, U29.1
unnamed: J19.13, U29.3
unnamed: J19.14, U29.5
unnamed: Q8.2 (G), R84.1, U29.7
unnamed: R80.1, U20.1 (GAIN)
unnamed: C52.2, TP10.1 (1_1), U20.3 (+)
unnamed: C51.1, U20.7 (BYPASS)
unnamed: U28.4, U29.4, U30.4 (B)
unnamed: U29.6, U32.4 (B)
PB12: U26.8
PB13: U26.6
PB14: U26.4
PB15: U26.2
PC6: R82.2
RGB_Data: J15.2
SPI1_MISO: U30.3 (A); also elsewhere on the board
SPI1_MOSI: U27.8, U29.2; also elsewhere on the board
SPI1_SCK: U28.2, U28.6; also elsewhere on the board
SWDCLK: J11.2, U18.3 (I/O2); also elsewhere on the board
SWDIO: J11.4, U18.4 (I/O3); also elsewhere on the board
Soft_Power: R81.2, R83.1
Speaker_DAC: R85.2
Touch_CS: U28.8
Touch_IRQ: U32.3 (A)
VAA: J19.1, JP13.2 (C), U30.6 (VCCB), U32.6 (VCCB)

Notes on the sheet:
Enclosure Fans
External Power/Reset Buttons
STLink Programmer
1N5819HW-7-F Datasheet
Fan 2
JST XH
4.0" Touch LCD
WS2812B Strip
Expandability Headers
Limit Switch Connector
Spare GPIO
4Ω Loudspeaker
WS2812B LED Strip
STLink
Fan 1
Power & Reset
Fan 3
Power
Padless and Chassis ground holes near AC side. GND holes on LV side
Use M3 mounting screws to secure PCB to housing
[${#}] ${TITLE}
